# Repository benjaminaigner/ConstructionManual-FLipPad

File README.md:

# FP_ConstructionManual

FLipPad Construction Manual

# Software

* Scribus for the page layout
* FreeCAD for the PCB & case renderings

## FreeCAD Plugins

Due to different extra features we need, some new workbenches (addons) must be installed to FreeCAD:

* __Render:__ Install this workbench via the integrated addon manager (Tools -> Addon manager)
* __Animate:__ Currently (02/2022), the animate workbench has to be installed manually: https://jirivalasek.github.io/Animate/Guide/getting_started.html

## Additional hints

### Converting the output PNGs from Animate to gif/avi

Quality is not very good for .avi:

`ffmpeg -i "seq20220228171006-%5d.png"  -framerate 12 -y out.avi`

.gif quality is acceptable, but quite a big output file:

`ffmpeg -i "seq20220228171006-%5d.png"  -framerate 6 -filter_complex  "fps=6,split=2[palette_in][gif];[palette_in]palettegen[palette_out];[gif]fifo[gif_fifo]; [gif_fifo][palette_out]paletteuse" -y image.gif`

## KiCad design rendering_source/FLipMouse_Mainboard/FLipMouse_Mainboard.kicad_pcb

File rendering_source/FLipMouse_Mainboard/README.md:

# This is a non-working KiCAD PCB for FLipMouse 2

This PCB file is currently not functioning, this is only for 3D rendering.
Next batches might be using this project instead of the EAGLE files.

# Usage

If you want to adapt the renderings or any parts of the PCB:

* Apply changes to the PCB
* Export the PCB into a STEP file (PCBNew -> File -> Export -> STEP)
* Create a new FreeCAD project (v0.17 recommended)
* Set background color to simple color, white (Edit->Preferences->Display)
* Import the STEP file into FreeCAD (File -> Import)
* Adjust colors manually:
	- LEDs
	- (PCB)
* Execute macro from the FreeCAD_Macro subdirectory
* Images 4&5 are positioned manually (to see the PCB top on the bottom with already mounted
01x02 +  02x05 headers and capacitors).
* Image 4 contains the headers, including the 2 01x14 + 01x05 headers for the Teensy
* Image 5 is with Teensy as well

__Note:__ The KiCAD parts are named within FreeCAD, so it is possible that names within the macro have to be changed!

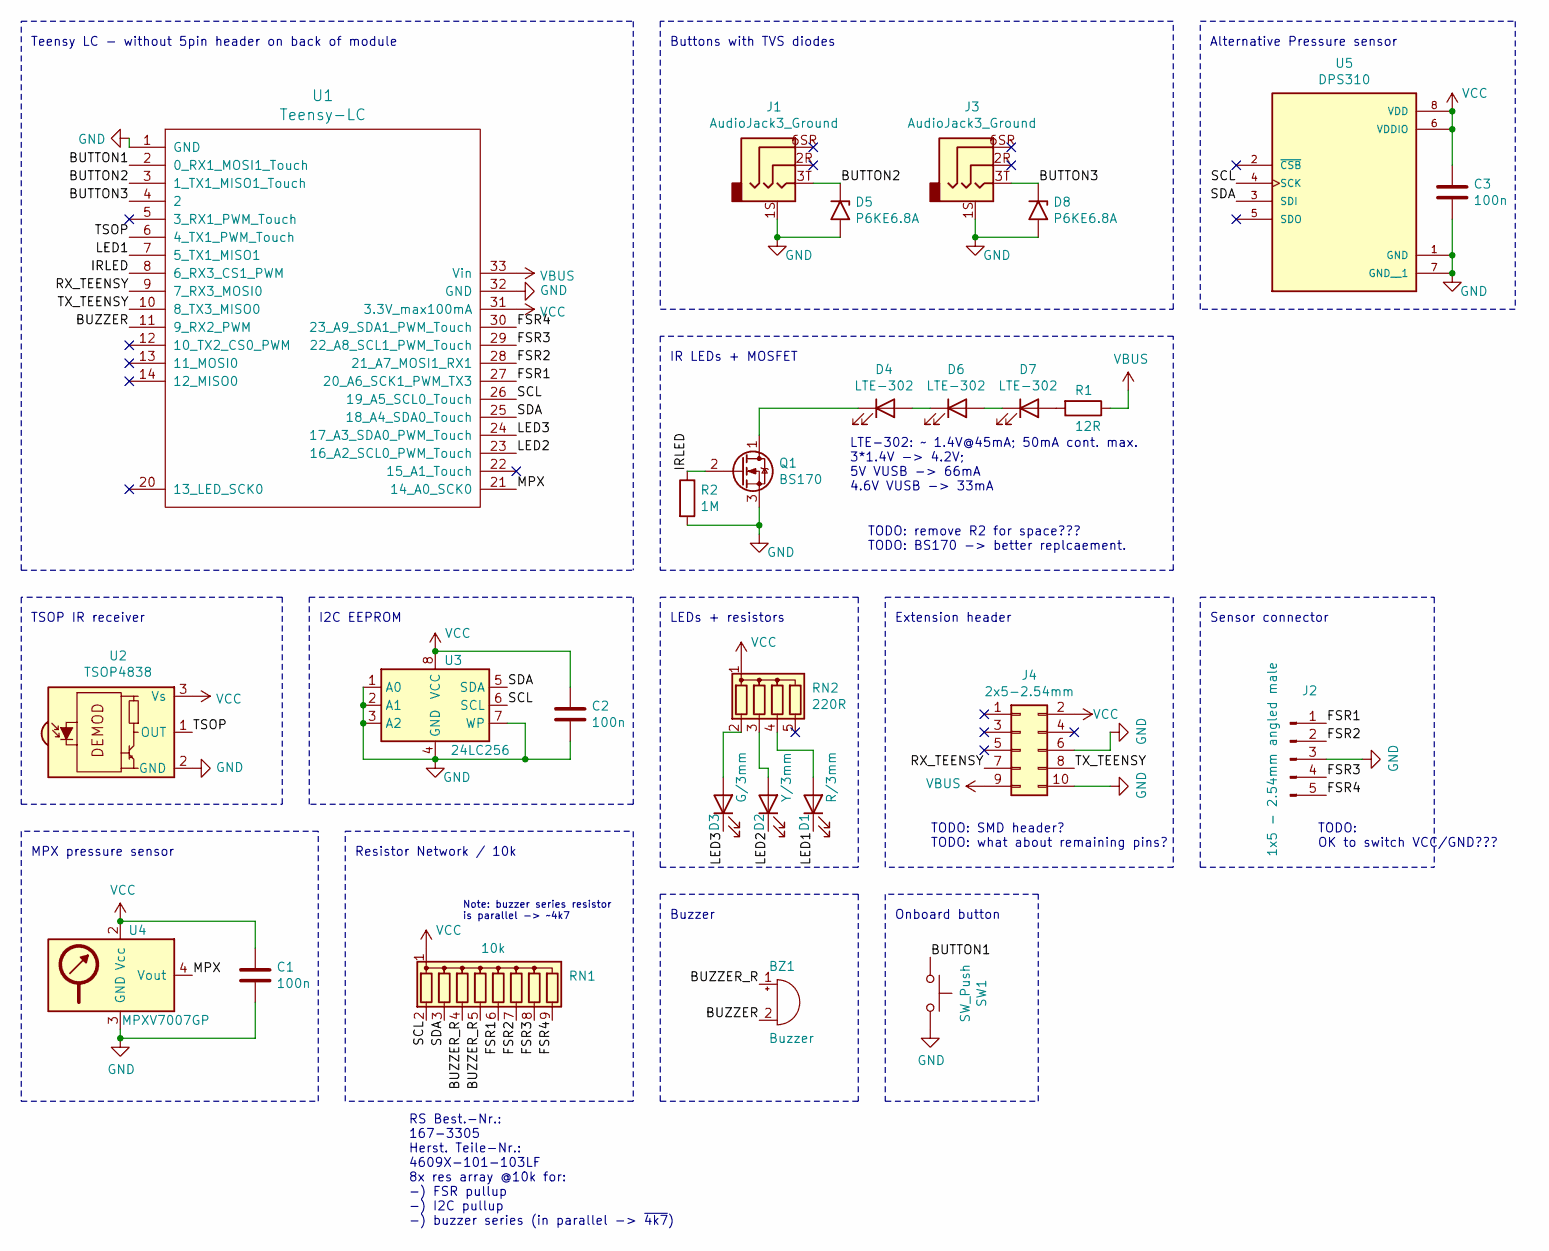
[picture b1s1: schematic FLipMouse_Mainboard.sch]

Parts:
BZ1: Buzzer; Buzzer_15x7.5RM7.6
C1, C2: 100n; C_Disc_D3.0mm_W2.0mm_P2.50mm
C3: 100n; C_0603_1608Metric_Pad1.08x0.95mm_HandSolder
D1: R/3mm; LED_D3.0mm_Horizontal_O1.27mm_Z2.0mm
D2: Y/3mm; LED_D3.0mm_Horizontal_O1.27mm_Z2.0mm
D3: G/3mm; LED_D3.0mm_Horizontal_O1.27mm_Z2.0mm
D4, D6, D7: LTE-302
D5, D8: P6KE6.8A; D_DO-201AE_P5.08mm_Vertical_KathodeUp
J1, J3: AudioJack3_Ground; FC68125
J2: 1x5 - 2.54mm angled male; PinHeader_1x05_P2.54mm_Horizontal
J4: 2x5-2.54mm; PinHeader_2x05_P2.54mm_Vertical
Q1: BS170; TO-92_Inline
R1: 12R; R_Axial_DIN0204_L3.6mm_D1.6mm_P1.90mm_Vertical
R2: 1M; R_Axial_DIN0204_L3.6mm_D1.6mm_P1.90mm_Vertical
RN1: 10k; R_Array_SIP9
RN2: 220R; R_Array_SIP5
SW1: SW_Push; SW_Tactile_SPST_Angled_PTS645Vx83-2LFS
U1: Teensy-LC; Teensy30_31_32_LC
U2: TSOP4838; Vishay_MOLD-3Pin
U3: 24LC256; DIP-8_W7.62mm
U4: MPXV7007GP
U5: DPS310

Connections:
/BUTTON1: SW1.1, U1.2 (0_RX1_MOSI1_Touch)
/BUTTON2: D5.1 (A1), J1.3T, U1.3 (1_TX1_MISO1_Touch)
/BUTTON3: D8.1 (A1), J3.3T, U1.4 (2)
/BUZZER: BZ1.2 (+), U1.11 (9_RX2_PWM)
/BUZZER_R: BZ1.1 (-), RN1.4 (R3), RN1.5 (R4)
/FSR1: J2.1, RN1.6 (R5), U1.27 (20_A6_SCK1_PWM_TX3)
/FSR2: J2.2, RN1.7 (R6), U1.28 (21_A7_MOSI1_RX1)
/FSR3: J2.4, RN1.8 (R7), U1.29 (22_A8_SCL1_PWM_Touch)
/FSR4: J2.5, RN1.9 (R8), U1.30 (23_A9_SDA1_PWM_Touch)
/IRLED: Q1.2 (G), R2.1, U1.8 (6_RX3_CS1_PWM)
/LED1: D1.1 (K), U1.7 (5_TX1_MISO1)
/LED2: D2.1 (K), U1.23 (16_A2_SCL0_PWM_Touch)
/LED3: D3.1 (K), U1.24 (17_A3_SDA0_PWM_Touch)
/MPX: U1.21 (14_A0_SCK0), U4.4 (Vout)
/RX_TEENSY: J4.7, U1.9 (7_RX3_MOSI0)
/SCL: RN1.2 (R1), U1.26 (19_A5_SCL0_Touch), U3.6 (SCL), U5.4 (SCK)
/SDA: RN1.3 (R2), U1.25 (18_A4_SDA0_Touch), U3.5 (SDA), U5.3 (SDI)
/TSOP: U1.6 (4_TX1_PWM_Touch), U2.1 (OUT)
/TX_TEENSY: J4.8, U1.10 (8_TX3_MISO0)
GND: C1.2, C2.2, C3.2, D5.2 (A2), D8.2 (A2), J1.1S, J2.3, J3.1S, J4.6, J4.10, Q1.3 (S), R2.2, SW1.2, U1.1 (GND), U1.32 (GND), U2.2 (GND), U3.1 (A0), U3.2 (A1), U3.3 (A2), U3.4 (GND), U3.7 (WP), U4.3 (GND), U5.1 (GND), U5.7 (GND__1)
unnamed: D1.2 (A), RN2.4 (R3)
unnamed: D2.2 (A), RN2.3 (R2)
unnamed: D3.2 (A), RN2.2 (R1)
unnamed: D4.1 (K), Q1.1 (D)
unnamed: D4.2 (A), D6.1 (K)
unnamed: D6.2 (A), D7.1 (K)
unnamed: D7.2 (A), R1.2
VBUS: J4.9, R1.1, U1.33 (Vin)
VCC: C1.1, C2.1, C3.1, J4.2, RN1.1 (common), RN2.1 (common), U1.31 (3.3V_max100mA), U2.3 (Vs), U3.8 (VCC), U4.2 (Vcc), U5.6 (VDDIO), U5.8 (VDD)

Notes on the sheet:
RS Best.-Nr.: 167-3305 Herst. Teile-Nr.: 4609X-101-103LF 8x res array @10k for: -) FSR pullup -) I2C pullup -) buzzer series (in parallel -> ~4k7)
MPX pressure sensor
TSOP IR receiver
Teensy LC - without 5pin header on back of module
I2C EEPROM
Resistor Network / 10k
Note: buzzer series resistor is parallel -> ~~4k7
Buzzer
LEDs + resistors
Extension header
TODO: SMD header? TODO: what about remaining pins?
TODO: OK to switch VCC/GND???
Sensor connector
Onboard button
LTE-302: ~~ 1.4V@45mA; 50mA cont. max. 3*1.4V -> 4.2V; 5V VUSB -> 66mA 4.6V VUSB -> 33mA
IR LEDs + MOSFET
TODO: remove R2 for space??? TODO: BS170 -> better replcaement.
Buttons with TVS diodes
Alternative Pressure sensor

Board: 2 copper layers, 27 parts (2 on the bottom side), 29 nets, no tracks yet.

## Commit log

2022-02-10 First draft
2022-02-28 Added requirement notes, added gitignore for FC; cleaned up FreeCAD project
2022-02-28 Added animation for assembly of case
2022-03-01 Updated assembly animation
2026-01-22 fixed typo
